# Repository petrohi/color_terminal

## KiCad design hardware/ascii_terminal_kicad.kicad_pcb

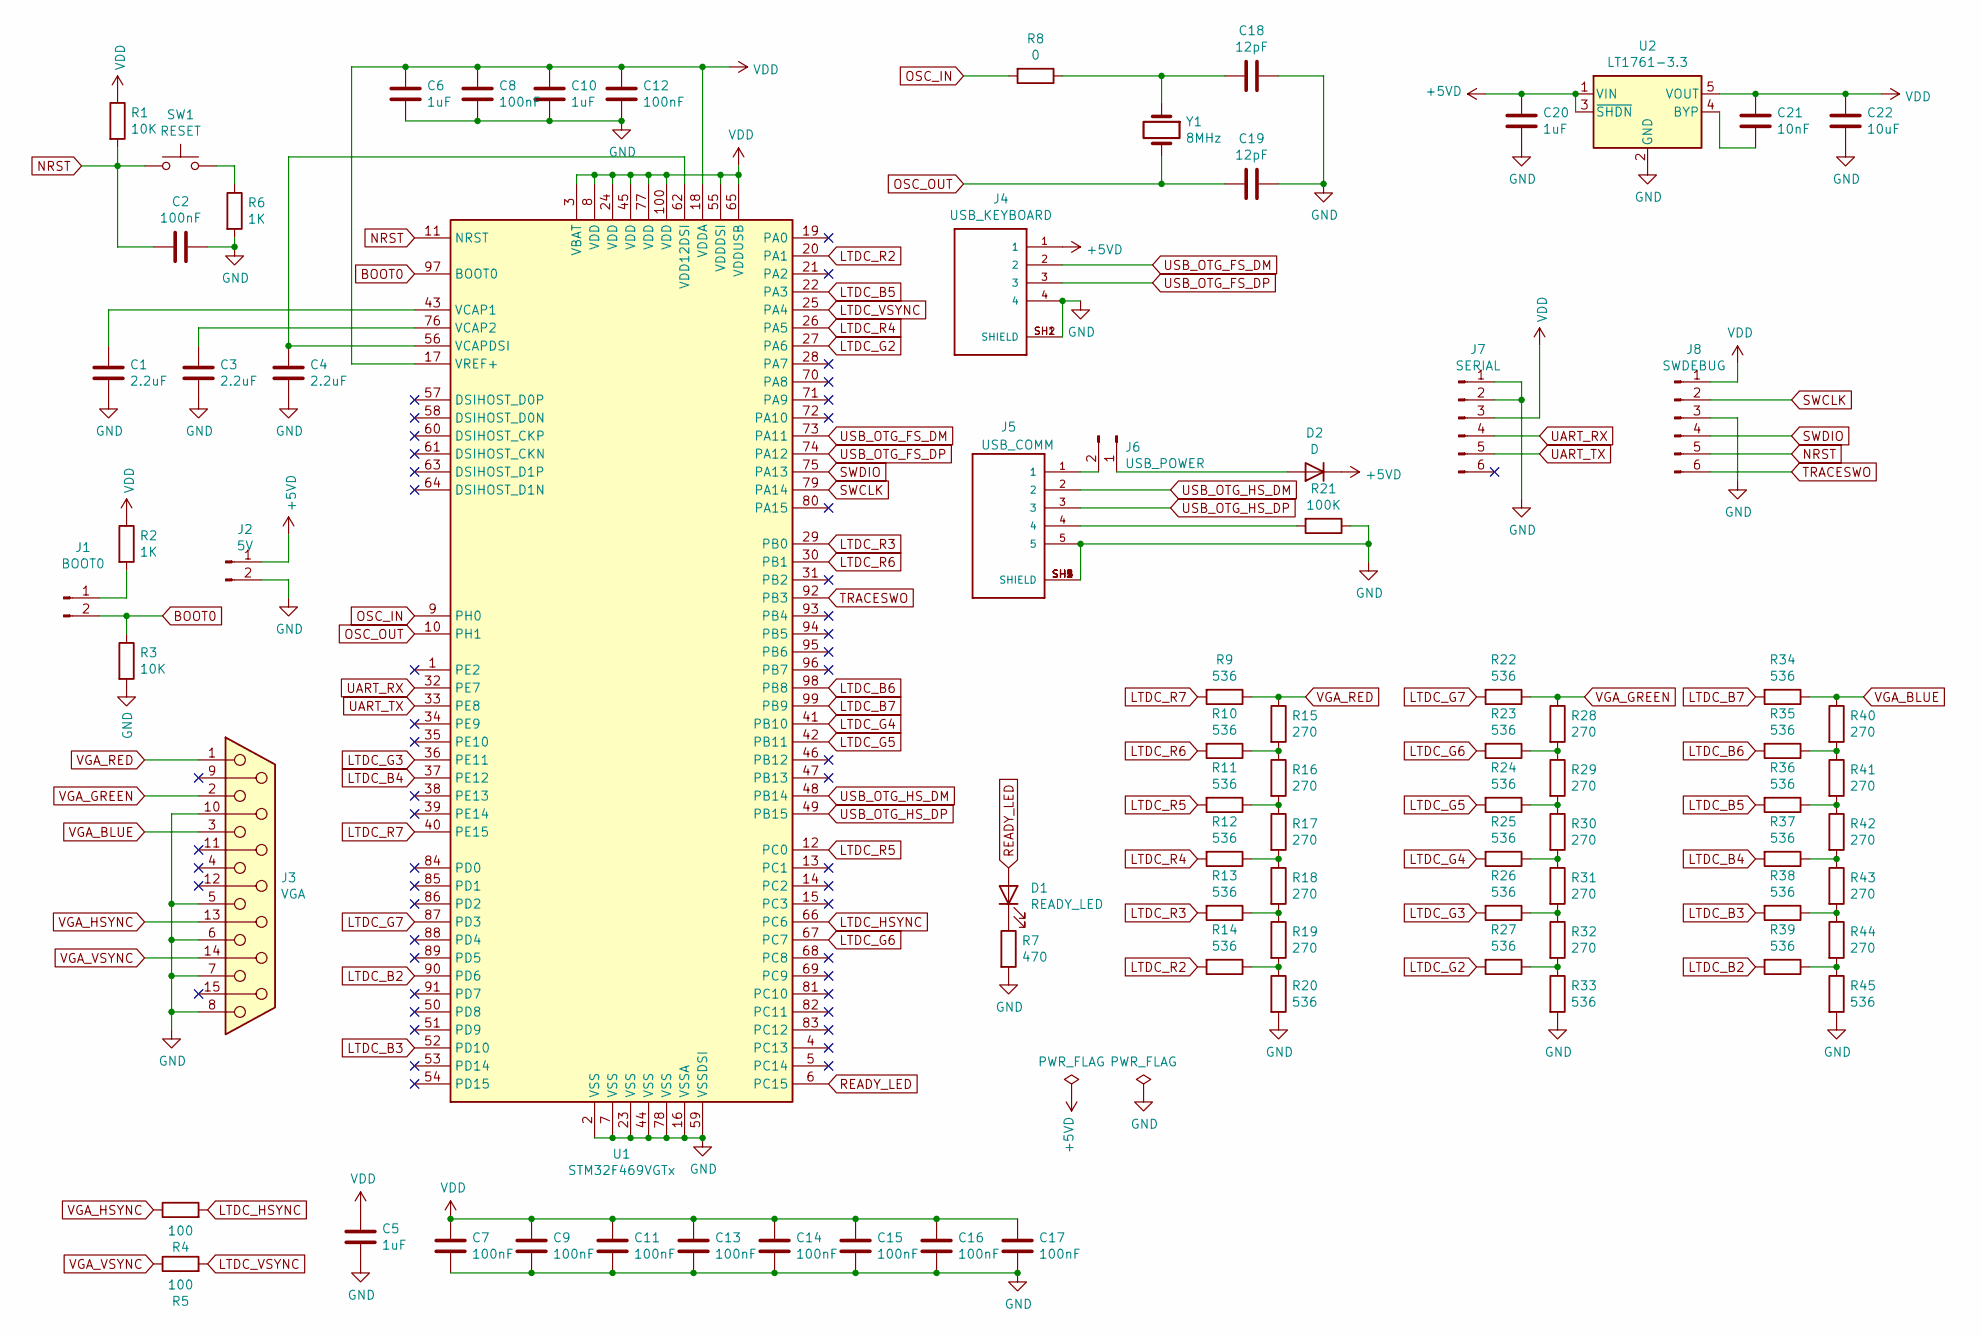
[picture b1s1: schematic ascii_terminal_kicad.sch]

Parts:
C1, C3, C4: 2.2uF; C_0805_2012Metric
C2, C7, C8, C9, C11, C12, C13, C14, C15, C16, C17: 100nF; C_0805_2012Metric
C5, C6, C10, C20: 1uF; C_0805_2012Metric
C18, C19: 12pF; C_0805_2012Metric
C21: 10nF; C_0805_2012Metric
C22: 10uF; C_0805_2012Metric
D1: READY_LED; LED_0805_2012Metric
D2: D; D_1206_3216Metric
J1: BOOT0; PinHeader_1x02_P2.54mm_Vertical
J2: 5V; PinHeader_1x02_P2.54mm_Vertical
J3: VGA; AMPHENOL_L77HDE15SD1CH4F
J4: USB_KEYBOARD; CUI_UJ2-AH-4-TH
J5: USB_COMM; CUI_UJ2-MIBH2-4-SMT
J6: USB_POWER; PinHeader_1x02_P2.54mm_Vertical
J7: SERIAL; PinHeader_1x06_P2.54mm_Vertical
J8: SWDEBUG; PinHeader_1x06_P2.54mm_Vertical
R1, R3: 10K; R_0805_2012Metric
R2, R6: 1K; R_0805_2012Metric
R4, R5: 100; R_0805_2012Metric
R7: 470; R_0805_2012Metric
R8: 0; R_0805_2012Metric
R9, R10, R11, R12, R13, R14, R20, R22, R23, R24, R25, R26, R27, R33, R34, R35, R36, R37, R38, R39, R45: 536; R_0805_2012Metric
R15, R16, R17, R18, R19, R28, R29, R30, R31, R32, R40, R41, R42, R43, R44: 270; R_0805_2012Metric
R21: 100K; R_0805_2012Metric
SW1: RESET; SW_SPST_FSMSM
U1: STM32F469VGTx; LQFP-100_14x14mm_P0.5mm
U2: LT1761-3.3; TSOT-23-5
Y1: 8MHz; Crystal_SMD_5032-2Pin_5.0x3.2mm

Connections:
+5VD: C20.1, D2.1 (K), J2.1, J4.1, U2.1 (VIN), U2.3 (~SHDN)
BOOT0: J1.2, R3.1, U1.97 (BOOT0)
GND: C1.2, C2.1, C3.2, C4.2, C5.2, C6.2, C7.2, C8.2, C9.2, C10.2, C11.2, C12.2, C13.2, C14.2, C15.2, C16.2, C17.2, C18.1, C19.1, C20.2, C22.2, J2.2, J3.5, J3.6, J3.7, J3.8, J3.10, J4.4, J4.SH1 (SHIELD), J4.SH2 (SHIELD), J5.5, J5.SH1 (SHIELD), J5.SH2 (SHIELD), J5.SH3 (SHIELD), J5.SH4 (SHIELD), J5.SH5 (SHIELD), J7.1, J7.2, J8.3, R3.2, R6.2, R7.2, R20.2, R21.1, R33.2, R45.2, U1.2 (VSS), U1.7 (VSS), U1.16 (VSSA), U1.23 (VSS), U1.44 (VSS), U1.59 (VSSDSI), U1.78 (VSS), U2.2 (GND)
LTDC_B2: R39.2, U1.90 (PD6)
LTDC_B3: R38.2, U1.52 (PD10)
LTDC_B4: R37.2, U1.37 (PE12)
LTDC_B5: R36.2, U1.22 (PA3)
LTDC_B6: R35.2, U1.98 (PB8)
LTDC_B7: R34.2, U1.99 (PB9)
LTDC_G2: R27.2, U1.27 (PA6)
LTDC_G3: R26.2, U1.36 (PE11)
LTDC_G4: R25.2, U1.41 (PB10)
LTDC_G5: R24.2, U1.42 (PB11)
LTDC_G6: R23.2, U1.67 (PC7)
LTDC_G7: R22.2, U1.87 (PD3)
LTDC_HSYNC: R4.2, U1.66 (PC6)
LTDC_R2: R14.2, U1.20 (PA1)
LTDC_R3: R13.2, U1.29 (PB0)
LTDC_R4: R12.2, U1.26 (PA5)
LTDC_R5: R11.2, U1.12 (PC0)
LTDC_R6: R10.2, U1.30 (PB1)
LTDC_R7: R9.2, U1.40 (PE15)
LTDC_VSYNC: R5.2, U1.25 (PA4)
NRST: C2.2, J8.5, R1.2, SW1.1, U1.11 (NRST)
unnamed: C1.1, U1.43 (VCAP1)
unnamed: C3.1, U1.76 (VCAP2)
unnamed: C4.1, U1.56 (VCAPDSI), U1.62 (VDD12DSI)
unnamed: C18.2, R8.1, Y1.1
unnamed: C21.2, U2.4 (BYP)
unnamed: D1.1 (K), R7.1
unnamed: D2.2 (A), J6.1
unnamed: J1.1, R2.2
unnamed: J5.1, J6.2
unnamed: J5.4, R21.2
unnamed: R6.1, SW1.2
unnamed: R10.1, R15.2, R16.1
unnamed: R11.1, R16.2, R17.1
unnamed: R12.1, R17.2, R18.1
unnamed: R13.1, R18.2, R19.1
unnamed: R14.1, R19.2, R20.1
unnamed: R23.1, R28.2, R29.1
unnamed: R24.1, R29.2, R30.1
unnamed: R25.1, R30.2, R31.1
unnamed: R26.1, R31.2, R32.1
unnamed: R27.1, R32.2, R33.1
unnamed: R35.1, R40.2, R41.1
unnamed: R36.1, R41.2, R42.1
unnamed: R37.1, R42.2, R43.1
unnamed: R38.1, R43.2, R44.1
unnamed: R39.1, R44.2, R45.1
OSC_IN: R8.2, U1.9 (PH0)
OSC_OUT: C19.2, U1.10 (PH1), Y1.2
READY_LED: D1.2 (A), U1.6 (PC15)
SWCLK: J8.2, U1.79 (PA14)
SWDIO: J8.4, U1.75 (PA13)
TRACESWO: J8.6, U1.92 (PB3)
UART_RX: J7.4, U1.32 (PE7)
UART_TX: J7.5, U1.33 (PE8)
USB_OTG_FS_DM: J4.2, U1.73 (PA11)
USB_OTG_FS_DP: J4.3, U1.74 (PA12)
USB_OTG_HS_DM: J5.2, U1.48 (PB14)
USB_OTG_HS_DP: J5.3, U1.49 (PB15)
VDD: C5.1, C6.1, C7.1, C8.1, C9.1, C10.1, C11.1, C12.1, C13.1, C14.1, C15.1, C16.1, C17.1, C21.1, C22.1, J7.3, J8.1, R1.1, R2.1, U1.3 (VBAT), U1.8 (VDD), U1.17 (VREF+), U1.18 (VDDA), U1.24 (VDD), U1.45 (VDD), U1.55 (VDDDSI), U1.65 (VDDUSB), U1.77 (VDD), U1.100 (VDD), U2.5 (VOUT)
VGA_BLUE: J3.3, R34.1, R40.1
VGA_GREEN: J3.2, R22.1, R28.1
VGA_HSYNC: J3.13, R4.1
VGA_RED: J3.1, R9.1, R15.1
VGA_VSYNC: J3.14, R5.1

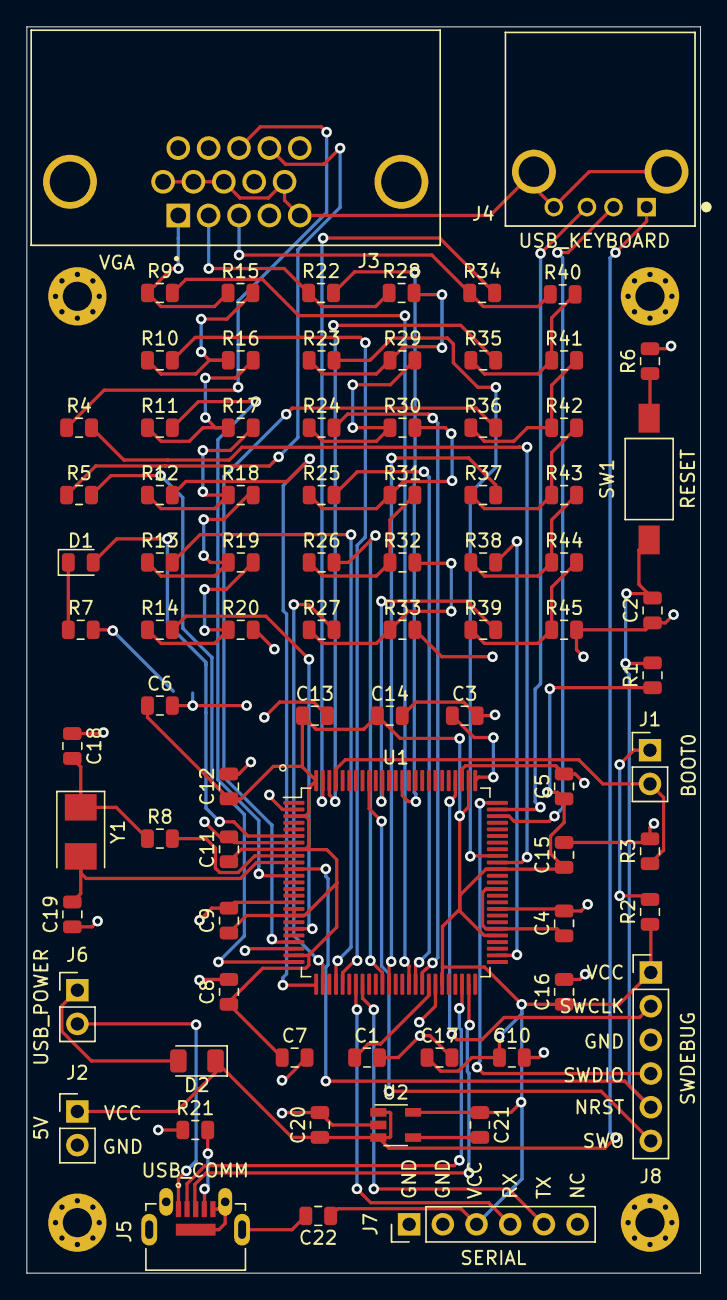
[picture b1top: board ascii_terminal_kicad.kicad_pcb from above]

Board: 2 copper layers, 50.8 x 94.0 mm, 85 parts (0 on the bottom side), 68 nets.

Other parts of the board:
REF1, REF2, REF3, REF4: MountingHole_2.2mm_M2_Pad_Via

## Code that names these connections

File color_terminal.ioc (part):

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PA6.Mode=RGB666
PC15/OSC32_OUT.GPIO_Label=READY_LED
Mcu.UserName=STM32F469VGTx
PB10.Mode=RGB666
PA11.Mode=Host_Only
PB11.Signal=LTDC_G5
PB15.Signal=USB_OTG_HS_DP
RCC.SYSCLKSource=RCC_SYSCLKSOURCE_PLLCLK
PA12.Signal=USB_OTG_FS_DP
PE11.Mode=RGB666
PA4.Mode=RGB666
PH0/OSC_IN.Mode=HSE-External-Oscillator
PC7.Signal=LTDC_G6
PH1/OSC_OUT.Signal=RCC_OSC_OUT
PD10.Mode=RGB666
RCC.HSE_VALUE=8000000
PC15/OSC32_OUT.GPIOParameters=GPIO_Label
PE13.Signal=LTDC_DE
PB14.Mode=Device_Only_FS
PE13.Mode=RGB666
PD3.Mode=RGB666
PH1/OSC_OUT.Mode=HSE-External-Oscillator
Mcu.Package=LQFP100
PB9.Signal=LTDC_B7
PB1.Signal=LTDC_R6
PA6.Signal=LTDC_G2
PE7.Signal=UART7_RX
PD6.Signal=LTDC_B2
PA3.Signal=LTDC_B5
PA5.Mode=RGB666
PE12.Mode=RGB666
PD3.Signal=LTDC_G7
PC6.Signal=LTDC_HSYNC
PC0.Signal=LTDC_R5
PD6.Mode=RGB666
PC0.Mode=RGB666
PE8.Mode=Asynchronous
PD10.Signal=LTDC_B3
PA3.Mode=RGB666
PB11.Mode=RGB666
PC6.Mode=RGB666
PB9.Mode=RGB666
PE11.Signal=LTDC_G3
PA1.Signal=LTDC_R2
PB10.Signal=LTDC_G4
PB14.Signal=USB_OTG_HS_DM
PA5.Signal=LTDC_R4
PB0.Mode=RGB666
board=custom
PB15.Mode=Device_Only_FS
PH0/OSC_IN.Signal=RCC_OSC_IN
PE14.Signal=LTDC_CLK
PA1.Mode=RGB666
PE15.Signal=LTDC_R7
PE8.Signal=UART7_TX
PE14.Mode=RGB666
Mcu.Name=STM32F469V(E-G)Tx
PE12.Signal=LTDC_B4
PA4.Signal=LTDC_VSYNC
RCC.SYSCLKFreq_VALUE=144000000
PE7.Mode=Asynchronous
PA12.Mode=Host_Only
PA11.Signal=USB_OTG_FS_DM
PB1.Mode=RGB666
PB8.Mode=RGB666
PB8.Signal=LTDC_B6
PC15/OSC32_OUT.Signal=GPIO_Output
PC7.Mode=RGB666
PB0.Signal=LTDC_R3
PE15.Mode=RGB666

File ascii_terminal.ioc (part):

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Mcu.Name=STM32F429ZITx
Mcu.Package=LQFP144
Mcu.UserName=STM32F429ZITx
PA11.GPIOParameters=GPIO_Speed,GPIO_PuPd,GPIO_Mode
PA11.GPIO_Mode=GPIO_MODE_AF_PP
PA11.GPIO_PuPd=GPIO_NOPULL
PA11.GPIO_Speed=GPIO_SPEED_FREQ_HIGH
PA11.Mode=RGB666
PA11.Signal=LTDC_R4
PA12.GPIOParameters=GPIO_Speed,GPIO_PuPd,GPIO_Mode
PA12.GPIO_Mode=GPIO_MODE_AF_PP
PA12.GPIO_PuPd=GPIO_NOPULL
PA12.GPIO_Speed=GPIO_SPEED_FREQ_HIGH
PA12.Mode=RGB666
PA12.Signal=LTDC_R5
PA13.Mode=Trace_Asynchronous_SW
PA13.Signal=SYS_JTMS-SWDIO
PA14.Mode=Trace_Asynchronous_SW
PA14.Signal=SYS_JTCK-SWCLK
PA3.GPIOParameters=GPIO_Speed,GPIO_PuPd,GPIO_Mode
PA3.GPIO_Mode=GPIO_MODE_AF_PP
PA3.GPIO_PuPd=GPIO_NOPULL
PA3.GPIO_Speed=GPIO_SPEED_FREQ_HIGH
PA3.Mode=RGB666
PA3.Signal=LTDC_B5
PA4.GPIOParameters=GPIO_Speed,GPIO_PuPd,GPIO_Mode
PA4.GPIO_Mode=GPIO_MODE_AF_PP
PA4.GPIO_PuPd=GPIO_NOPULL
PA4.GPIO_Speed=GPIO_SPEED_FREQ_HIGH
PA4.Mode=RGB666
PA4.Signal=LTDC_VSYNC
PA6.GPIOParameters=GPIO_Speed,GPIO_PuPd,GPIO_Mode
PA6.GPIO_Mode=GPIO_MODE_AF_PP
PA6.GPIO_PuPd=GPIO_NOPULL
PA6.GPIO_Speed=GPIO_SPEED_FREQ_HIGH
PA6.Mode=RGB666
PA6.Signal=LTDC_G2
PB0.GPIOParameters=GPIO_Speed,GPIO_PuPd,GPIO_Mode
PB0.GPIO_Mode=GPIO_MODE_AF_PP
PB0.GPIO_PuPd=GPIO_NOPULL
PB0.GPIO_Speed=GPIO_SPEED_FREQ_HIGH
PB0.Mode=RGB666
PB0.Signal=LTDC_R3
PB1.GPIOParameters=GPIO_Speed,GPIO_PuPd,GPIO_Mode
PB1.GPIO_Mode=GPIO_MODE_AF_PP
PB1.GPIO_PuPd=GPIO_NOPULL
PB1.GPIO_Speed=GPIO_SPEED_FREQ_HIGH
PB1.Mode=RGB666
PB1.Signal=LTDC_R6
PB10.GPIOParameters=GPIO_Speed,GPIO_PuPd,GPIO_Mode
PB10.GPIO_Mode=GPIO_MODE_AF_PP
PB10.GPIO_PuPd=GPIO_NOPULL
PB10.GPIO_Speed=GPIO_SPEED_FREQ_HIGH
PB10.Mode=RGB666
PB10.Signal=LTDC_G4
PB11.GPIOParameters=GPIO_Speed,GPIO_PuPd,GPIO_Mode
PB11.GPIO_Mode=GPIO_MODE_AF_PP
PB11.GPIO_PuPd=GPIO_NOPULL
PB11.GPIO_Speed=GPIO_SPEED_FREQ_HIGH
PB11.Mode=RGB666
PB11.Signal=LTDC_G5
PB14.GPIOParameters=GPIO_Speed,GPIO_PuPd,GPIO_Mode
PB14.GPIO_Mode=GPIO_MODE_AF_PP
PB14.GPIO_PuPd=GPIO_NOPULL
PB14.GPIO_Speed=GPIO_SPEED_FREQ_VERY_HIGH
PB14.Mode=Host_FS
PB14.Signal=USB_OTG_HS_DM
PB15.GPIOParameters=GPIO_Speed,GPIO_PuPd,GPIO_Mode
PB15.GPIO_Mode=GPIO_MODE_AF_PP
PB15.GPIO_PuPd=GPIO_NOPULL
PB15.GPIO_Speed=GPIO_SPEED_FREQ_VERY_HIGH
PB15.Mode=Host_FS
PB15.Signal=USB_OTG_HS_DP
PB3.Mode=Trace_Asynchronous_SW
PB3.Signal=SYS_JTDO-SWO
PB5.Mode=SdramChipSelect2_1
PB5.Signal=FMC_SDCKE1
PB6.Mode=SdramChipSelect2_1
PB6.Signal=FMC_SDNE1
PB8.GPIOParameters=GPIO_Speed,GPIO_PuPd,GPIO_Mode
PB8.GPIO_Mode=GPIO_MODE_AF_PP
PB8.GPIO_PuPd=GPIO_NOPULL
PB8.GPIO_Speed=GPIO_SPEED_FREQ_HIGH
PB8.Mode=RGB666
PB8.Signal=LTDC_B6
PB9.GPIOParameters=GPIO_Speed,GPIO_PuPd,GPIO_Mode
PB9.GPIO_Mode=GPIO_MODE_AF_PP
PB9.GPIO_PuPd=GPIO_NOPULL
PB9.GPIO_Speed=GPIO_SPEED_FREQ_HIGH
PB9.Mode=RGB666
PB9.Signal=LTDC_B7
PC0.Signal=FMC_SDNWE
PC10.GPIOParameters=GPIO_Speed
PC10.GPIO_Speed=GPIO_SPEED_FREQ_HIGH
PC10.Mode=RGB666
PC10.Signal=LTDC_R2
PC4.GPIOParameters=GPIO_Label
PC4.GPIO_Label=USB_OTG_HS_DRIVE_VBUS
PC4.Signal=GPIO_Output
PC6.GPIOParameters=GPIO_Speed,GPIO_PuPd,GPIO_Mode
PC6.GPIO_Mode=GPIO_MODE_AF_PP
PC6.GPIO_PuPd=GPIO_NOPULL
PC6.GPIO_Speed=GPIO_SPEED_FREQ_HIGH
PC6.Mode=RGB666
PC6.Signal=LTDC_HSYNC
PC7.GPIOParameters=GPIO_Speed,GPIO_PuPd,GPIO_Mode
PC7.GPIO_Mode=GPIO_MODE_AF_PP
PC7.GPIO_PuPd=GPIO_NOPULL
PC7.GPIO_Speed=GPIO_SPEED_FREQ_HIGH
PC7.Mode=RGB666
PC7.Signal=LTDC_G6
PD0.Signal=FMC_D2_DA2
PD1.Signal=FMC_D3_DA3
PD10.Signal=FMC_D15_DA15
PD14.Signal=FMC_D0_DA0
PD15.Signal=FMC_D1_DA1
PD3.GPIOParameters=GPIO_Speed,GPIO_PuPd,GPIO_Mode
PD3.GPIO_Mode=GPIO_MODE_AF_PP
PD3.GPIO_PuPd=GPIO_NOPULL
PD3.GPIO_Speed=GPIO_SPEED_FREQ_HIGH
PD3.Mode=RGB666
PD3.Signal=LTDC_G7
PD6.GPIOParameters=GPIO_Speed
PD6.GPIO_Speed=GPIO_SPEED_FREQ_HIGH
PD6.Mode=RGB666
PD6.Signal=LTDC_B2
PD8.Signal=FMC_D13_DA13
PD9.Signal=FMC_D14_DA14
PE0.Signal=FMC_NBL0
PE1.Signal=FMC_NBL1
PE10.Signal=FMC_D7_DA7
PE11.Signal=FMC_D8_DA8
PE12.Signal=FMC_D9_DA9
PE13.Signal=FMC_D10_DA10
PE14.Signal=FMC_D11_DA11
PE15.Signal=FMC_D12_DA12
PE7.Signal=FMC_D4_DA4
PE8.Signal=FMC_D5_DA5
PE9.Signal=FMC_D6_DA6
PF0.Signal=FMC_A0
PF1.Signal=FMC_A1
PF10.GPIOParameters=GPIO_Speed,GPIO_PuPd,GPIO_Mode
PF10.GPIO_Mode=GPIO_MODE_AF_PP
PF10.GPIO_PuPd=GPIO_NOPULL
PF10.GPIO_Speed=GPIO_SPEED_FREQ_HIGH
PF10.Mode=RGB666
PF10.Signal=LTDC_DE
PF11.Signal=FMC_SDNRAS
PF12.Signal=FMC_A6
PF13.Signal=FMC_A7
PF14.Signal=FMC_A8
PF15.Signal=FMC_A9
PF2.Signal=FMC_A2
PF3.Signal=FMC_A3
PF4.Signal=FMC_A4
PF5.Signal=FMC_A5
PF6.Mode=Asynchronous
PF6.Signal=UART7_RX
PF7.Mode=Asynchronous
PF7.Signal=UART7_TX
PG0.Signal=FMC_A10
PG1.Signal=FMC_A11
PG10.GPIOParameters=GPIO_Speed,GPIO_PuPd,GPIO_Mode
PG10.GPIO_Mode=GPIO_MODE_AF_PP
PG10.GPIO_PuPd=GPIO_NOPULL
PG10.GPIO_Speed=GPIO_SPEED_FREQ_HIGH
PG10.Mode=RGB666
PG10.Signal=LTDC_G3
PG11.GPIOParameters=GPIO_Speed,GPIO_PuPd,GPIO_Mode
PG11.GPIO_Mode=GPIO_MODE_AF_PP
PG11.GPIO_PuPd=GPIO_NOPULL
PG11.GPIO_Speed=GPIO_SPEED_FREQ_HIGH
PG11.Mode=RGB666
PG11.Signal=LTDC_B3
PG12.GPIOParameters=GPIO_Speed,GPIO_PuPd,GPIO_Mode
PG12.GPIO_Mode=GPIO_MODE_AF_PP
PG12.GPIO_PuPd=GPIO_NOPULL
PG12.GPIO_Speed=GPIO_SPEED_FREQ_HIGH
PG12.Mode=RGB666
PG12.Signal=LTDC_B4
PG15.Signal=FMC_SDNCAS
PG4.Signal=FMC_A14_BA0
PG5.Signal=FMC_A15_BA1
PG6.GPIOParameters=GPIO_Speed,GPIO_PuPd,GPIO_Mode
PG6.GPIO_Mode=GPIO_MODE_AF_PP
PG6.GPIO_PuPd=GPIO_NOPULL
PG6.GPIO_Speed=GPIO_SPEED_FREQ_HIGH
PG6.Mode=RGB666
PG6.Signal=LTDC_R7
PG7.GPIOParameters=GPIO_Speed,GPIO_PuPd,GPIO_Mode
PG7.GPIO_Mode=GPIO_MODE_AF_PP
PG7.GPIO_PuPd=GPIO_NOPULL
PG7.GPIO_Speed=GPIO_SPEED_FREQ_HIGH
PG7.Mode=RGB666
PG7.Signal=LTDC_CLK
PG8.Signal=FMC_SDCLK
PH0/OSC_IN.Mode=HSE-External-Oscillator
PH0/OSC_IN.Signal=RCC_OSC_IN
PH1/OSC_OUT.Mode=HSE-External-Oscillator
PH1/OSC_OUT.Signal=RCC_OSC_OUT
RCC.HSE_VALUE=8000000
RCC.SYSCLKFreq_VALUE=144000000
RCC.SYSCLKSource=RCC_SYSCLKSOURCE_PLLCLK
board=STM32F429I-DISC1
boardIOC=true

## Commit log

2020-05-26 Mandelbrot test
2020-06-01 Color with CLUT
2020-06-01 Adjust .gitignore
2020-06-07 Interactive Mandelbrot test
2020-06-07 DMA for UART
2020-06-08 UART transmit
2020-06-08 Print current Mandelbrot window to UART
2020-06-11 Circular DMA mode for UART receive
2020-06-11 6-bit RGB
2020-06-13 Keyboard state machine
2020-06-14 Receive from UART and draw characters
2020-06-14 Blinking cursor
2020-06-18 Key repetition
2020-06-19 Handle HVP control sequence
2020-06-19 Scrolling
2020-06-20 Handle SGR control sequence
2020-06-20 More control sequences
2020-06-20 Handle main keyboard
2020-06-20 Split terminal into UART, keyboard and screen modules
2020-06-20 Handle ctrl-keys
2020-06-21 Enable/disable cursor
2020-06-21 Save/restore visual state
2020-06-21 Printf unexpected control sequence
2020-06-21 Auto-wrap mode
2020-06-23 Enough space for leading zeroes in CSI params
2020-06-23 Default auto-wrap mode to reset
2020-06-23 Set UART to 38400 baud rate
2020-06-24 Support characters in upper ASCII table
2020-06-24 Modes
2020-06-25 Insert/delete/erase characters. Absolute vertical/horizontal position.
2020-06-26 Insert/delete lines
2020-06-27 Top/bottom margin
2020-06-28 Tab stops. Printf control sequences.
2020-06-28 Origin
2020-06-28 Fix scrolling
2020-06-29 Transmit NUL for Ctrl+Space and Ctrl+2
2020-06-29 Fix transmit printf
2020-06-30 Screen mode
2020-07-01 Blinking. Cells.
2020-07-01 Cursor keys
2020-07-02 VT52 mode
2020-07-02 UTF8--WIP
2020-07-03 UTF8 decoding. DEC special graphics. UW ttyp0 font and bdf2c.
2020-07-03 Graphic sets and codepoint transformation
2020-07-04 Back to font-problems. Handle UTF8 via receive tables.
2020-07-04 Default background to use SGR color
2020-07-04 Move receive logic outside of terminal core
2020-07-04 Editing keys
2020-07-04 Numeric pad keys
2020-07-04 Handle control data
2020-07-04 Handle DECREQTPARM
2020-07-04 Receive 8-bit control
2020-07-04 Ignore unsupported 8-bit controls
2020-07-05 C1 mode for 8-bit sending control
2020-07-05 Local echo mode
2020-07-05 Log unhandled controls only
2020-07-07 Use USART3. Flow control with XON/OFF.
2020-07-08 Simplify peripherals code
2020-07-08 Hello config!
2020-07-10 Config UI and flash
2020-07-11 Backspace mode
2020-07-12 Finalize config UI
2020-07-12 Move write config out of config UI
2020-07-12 Get baud rate as uint32_t
2020-07-18 Missing file
2020-07-18 Parametrize screen
2020-07-18 Configurable rows and columns
2020-07-18 Encapsulate rows and columns in format
2020-07-18 XC32 compatibility
2020-07-19 Monochrome screen
2020-07-19 PS/2 keyboard
2020-07-19 Circular buffering for UART transmit
2020-07-19 XOFF limit 256 bytes
2020-07-20 Byte-aligned monochrome VGA buffer
2020-07-20 RGB table
2020-07-20 Monochrome configuration
2020-07-21 Constant luminance table
2020-07-24 Full-res VGA on external SDRAM
2020-07-26 Yield to probe keyboard
2020-07-26 Static variables
2020-07-28 Clear screen line for monochrome
2020-07-28 Use local buffer for echo mode
2020-07-28 Fix SD/SU
2020-07-29 Probe keyboard when in config UI
2020-07-29 Optimize character rendering
2020-07-30 Fix CHA
2020-07-30 Terminus bold and normal fonts
2020-07-31 Config for flow control and inverted serial
2020-07-31 Start-up message
2020-07-31 Re-use terminal keyboard driver for config UI
2020-08-01 IBM PC charset. HPR, VPR, REP, CHT, CBT controls. Separate receive and transmit C1 modes.
2020-08-02 Fix line-wrapping semantics according DEC STD-070 with wraptest
2020-08-02 Fix color adjustments when rendering character
2020-08-03 Handle secondary DA and DECSTR
2020-08-03 Adjust F1-F4 codes
2020-08-04 Support 30 rows mode to use full VGA resolution
2020-08-05 Shift-Alt-Ctrl modifiers
2020-08-05 Configurable monochrome transformation
2020-08-06 Alternative cells
2020-08-06 Remove support for screen buffer padding
2020-08-06 Adjust config UI copy
2020-08-06 Clear screen when alternative cells are not supported
2020-08-08 Keyboard compatibility: PC/Sun and VT220
2020-08-09 Externalize tab stops and cells memory. Use bitset for tab stops.
2020-10-07 Configuration for application keypad mode
2020-11-14 UK keyboard layout
2020-11-16 Port to STM32F469VGTx
2020-11-16 Fix UART NVIC settings
2020-11-16 Config in flash memory
2020-11-16 Adjust keyboard initialization
2020-11-16 Fix CLUT for RGB2-7 pins reversed
2020-11-16 Set ready LED at the end of initialization
2020-11-20 Adjust TIM1 prescaler for higher APB2 clock
2020-11-20 Adjust GitHub link
2020-11-21 Hardware
2020-11-22 Hardware .gitignore
2020-11-22 Fix RGB bits order in schematic
2020-11-22 Cleanup tracks and vias
2020-12-05 Re-route

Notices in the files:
hardware/ascii_terminal_kicad.kicad_pcb:
Copyright (C) 2019-2020 Peter Hizalev
